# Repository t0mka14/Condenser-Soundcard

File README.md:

# Condenser-Soundcard
High gain USB soundcard with 5V power for headset condenser microphones.
This repo contains Kicad design files for a USB soundcard using PCM2912. It is basically a catalogue schematic, with the exception that there is a voltage pump to step up the DC bias voltage to 5V. We use this soundcard in our team at FEE CTU to record patients with various neurodegenerative diseases (https://sami.fel.cvut.cz/). I also include stl files with a box for the soundcard. Below you can find some graphs of parameters which I measured:

TODO

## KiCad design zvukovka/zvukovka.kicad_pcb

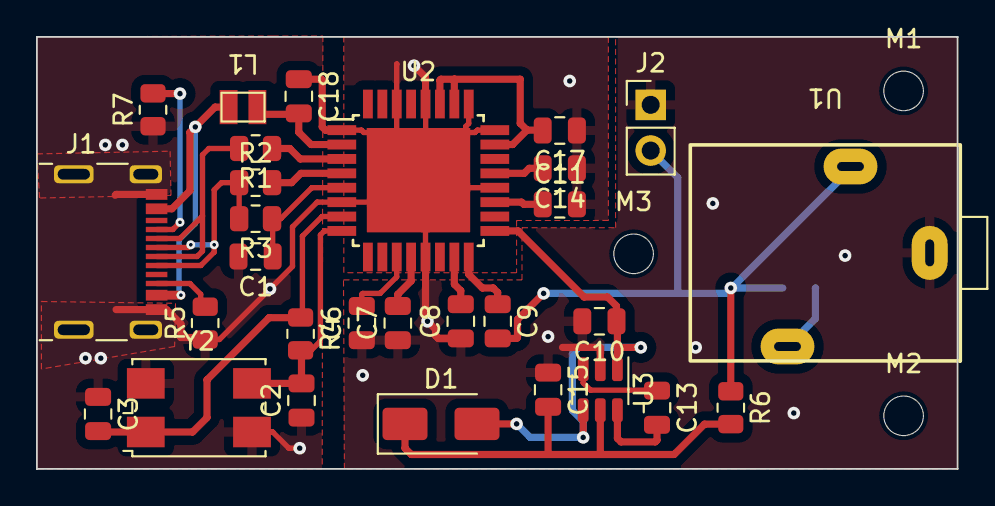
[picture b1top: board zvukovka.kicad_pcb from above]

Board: 2 copper layers, 51.2 x 24.0 mm, 33 parts (1 on the bottom side), 28 nets.

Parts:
C1, C8, C11, C14, C17, C18: 1u; C_0805_2012Metric
C2, C3: 22p; C_0805_2012Metric
C6, C10, C13, C15: 3.3u; C_0805_2012Metric
C7: 100n; C_0805_2012Metric
C9: 0.47u; C_0805_2012Metric
D1: D_Schottky; D_SMA
J1: USB_C_Receptacle_USB2.0; Conn_USB_C_Socket_Molex_2171790001
J2: Conn_01x02_Pin; PinHeader_1x02_P2.54mm_Vertical
L1: 1u; SRP2012TMA
M1, M2, M3: MountingHole_2.2mm_M2_DIN965
R1, R2: 33; R_0805_2012Metric
R3: 1.5k; R_0805_2012Metric
R4: 1M; R_0805_2012Metric
R5, R7: 5k1; R_0805_2012Metric
R6: 5k; R_0805_2012Metric
R8: R; R_0805_2012Metric
U1: AudioJackShare; K3612A
U2: PCM2912APJTR; TQFP-32_7x7mm_P0.8mm_netTie
U3: LM2766; SOT-23-6
Y2: Crystal_GND24; Crystal_SMD_7050-4Pin_7.0x5.0mm

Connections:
/USBC_D+: J1.A6 (D+), J1.B6 (D+), R2.1, R3.2
/XTO: C3.2, R4.1, U2.7 (XTO), Y2.1
CAPOUT: C15.2, D1.1 (K), R6.2, U3.5 (VOUT)
GND: C11.2, C14.1, C17.1, U2.20 (HGND), U2.24 (POWER), U2.25 (PGND), U2.28 (TEST0), U2.30 (MMUTE)
GND1: C18.1, U2.1 (BGND)
GNDA: C6.1, C7.1, C8.1, C10.2, C15.1, J2.1, U1.1, U2.13 (AGND), U3.2 (GND)
GNDD: C1.2, C2.1, C3.1, J1.A1 (GND), J1.S1 (SHIELD), R5.1, R7.1, U2.6 (DGND), Y2.2, Y2.4
unnamed: C10.1, D1.2 (A), U2.17 (MBIAS), U3.1 (V+), U3.4 (SD)
unnamed: J1.A5 (CC1), R7.2
unnamed: J1.B5 (CC2), R5.2
unnamed: J1.A7 (D-), J1.B7 (D-), R1.2
unnamed: J1.A4 (VBUS), L1.2
unnamed: R8.1, U1.3
unnamed: R2.2, U2.4 (D+)
unnamed: R1.1, U2.3 (D-)
unnamed: C17.2, U2.23 (MAMP), U2.26 (VCCP), U2.27 (TEST1)
unnamed: C18.2, L1.1, U2.2 (VBUS)
unnamed: C8.2, U2.15 (VCCA)
unnamed: C11.1, U2.19 (VCCL)
unnamed: C14.2, U2.21 (VCCR)
unnamed: C6.2, U2.11 (VCOM1)
unnamed: C7.2, U2.12 (VCOM2)
unnamed: C1.1, R3.1, U2.5 (VDD)
unnamed: C9.1, U2.16 (VIN)
unnamed: C2.2, R4.2, U2.8 (XTI), Y2.3
unnamed: C13.2, U3.6 (CAP+)
unnamed: C13.1, U3.3 (CAP-)
VIN: C9.2, J2.2, R6.1, R8.2, U1.2

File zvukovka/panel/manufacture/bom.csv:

"Reference","Value","Footprint","MPN","note","Qty"
"C1, C8, C11, C14, C17, C18","1u","Capacitor_SMD:C_0805_2012Metric","","X5R nebo X7R, >16V,10%","6"
"C2, C3","22p","Capacitor_SMD:C_0805_2012Metric","","X5R nebo X7R, >16V,10%","2"
"C6, C10, C13, C15","3.3u","Capacitor_SMD:C_0805_2012Metric","","X5R nebo X7R, >16V,10%","4"
"C7","100n","Capacitor_SMD:C_0805_2012Metric","","X5R nebo X7R, >16V,10%","1"
"C9","0.47u","Capacitor_SMD:C_0805_2012Metric","","X5R nebo X7R, >16V,10%","1"
"D1","D_Schottky","Diode_SMD:D_SMA","SS26A+","","1"
"J1","USB_C_Receptacle_USB2.0","zvukovka_2:Conn_USB_C_Socket_Molex_2171790001","217179-0001","","1"
"J2","Conn_01x02_Pin","Connector_PinHeader_2.54mm:PinHeader_1x02_P2.54mm_Vertical","","NEOSAZOVAT","1"
"L1","1u","zvukovka:SRP2012TMA","SRP2012TMA-1R0M","","1"
"M1-M3","MountingHole","MountingHole:MountingHole_2.2mm_M2_DIN965","","","3"
"R1, R2","33","Resistor_SMD:R_0805_2012Metric","","1%","2"
"R3","1.5k","Resistor_SMD:R_0805_2012Metric","","1%","1"
"R4","1M","Resistor_SMD:R_0805_2012Metric","","1%","1"
"R5, R7","5k1","Resistor_SMD:R_0805_2012Metric","","1%","2"
"R6","5k","Resistor_SMD:R_0805_2012Metric","","1%","1"
"U1","AudioJackShare","zvukovka_2:K3612A","K3612A","https://www.gme.cz/v/1501048/k3612a-jack-35-stereo","1"
"U2","PCM2912APJTR","zvukovka_2:TQFP-32_7x7mm_P0.8mm_netTie","PCM2912APJT","","1"
"U3","LM2766","Package_TO_SOT_SMD:SOT-23-6","LM2766M6X/NOPB","","1"
"Y2","Crystal_GND24","Crystal:Crystal_SMD_7050-4Pin_7.0x5.0mm","EA5070PA20-6.000M TR","","1"

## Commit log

2024-07-30 added kicad files
2024-07-30 added case
2025-04-13 init commit
2025-04-13 added images
